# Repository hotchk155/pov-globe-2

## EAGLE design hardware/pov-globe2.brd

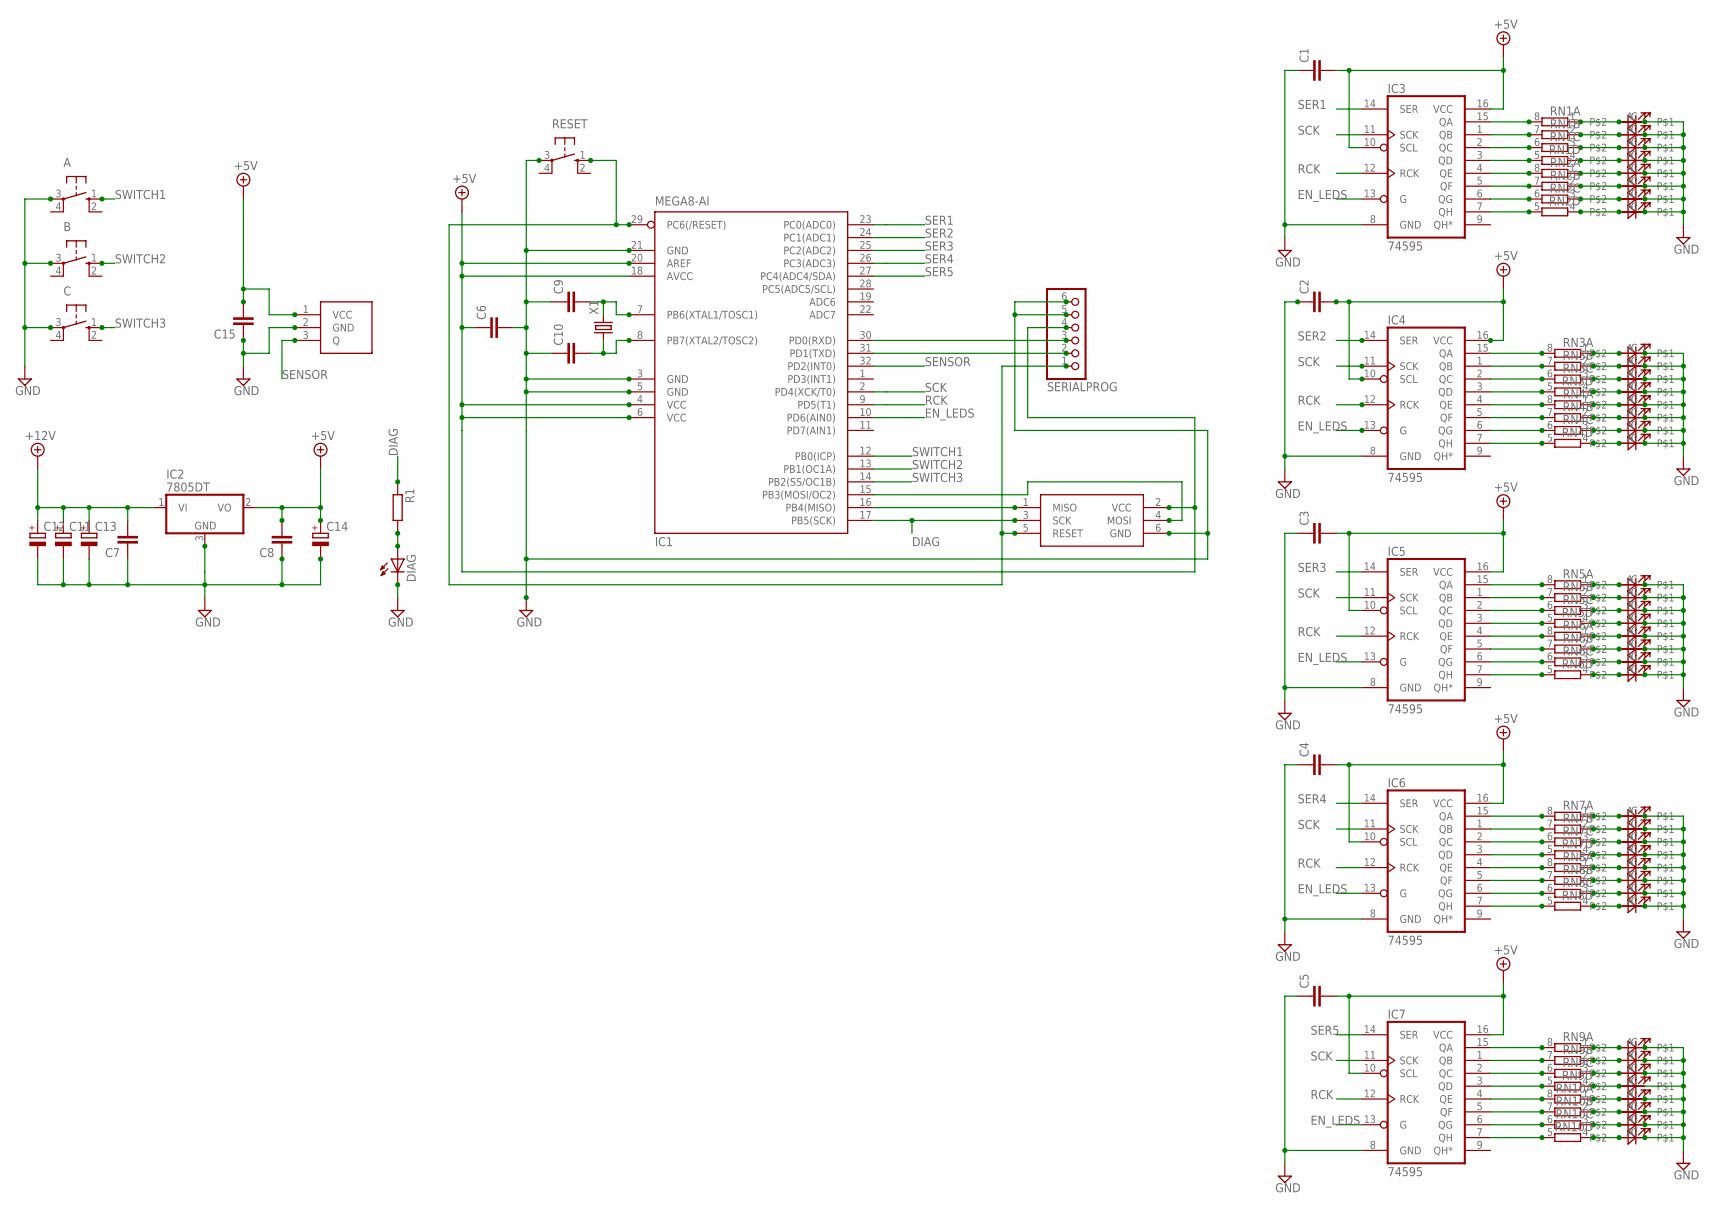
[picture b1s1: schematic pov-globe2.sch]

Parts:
0, 1, 2, 3, 4, 5, 6, 7, 8, 9, 10, 11, 12, 13, 14, 15, 16, 17, 18, 19, 20, 21, 22, 23, 24, 25, 26, 27, 28, 29, 30, 31, 32, 33, 34, 35, 36, 37, 38, 39: 3MMLEDSIDELED1_8MMSIDE; LED1_8MMSIDE
A: 10-XX; B3F-10XX
B: 10-XX; B3F-10XX
C: 10-XX; B3F-10XX
C1, C2, C3, C4, C5, C6, C7, C8, C9, C10, C15: C-EUC0805; C0805
C11, C12, C13, C14: CPOL-EUE2-5; E2-5
DIAG: LEDCHIP-LED0805; CHIP-LED0805
IC1: MEGA8-AI; TQFP32-08
IC2: 7805DT; TO252
IC3, IC4, IC5, IC6, IC7: 74595; TSSOP16
ICSP: TAG_CONN_AVR; TC2030-MCP-NL
R1: R-EU_R0805; R0805
RESET: 10-XX; B3F-10XX
RN1, RN2, RN3, RN4, RN5, RN6, RN7, RN8, RN9, RN10: 4R-N0603-ARC; 0603-ARC
S1: 3144HALLSWITCH
SERIALPROG: PINHD-1X6; 1X06
X1: CRYSTALHC49U-V; HC49U-V

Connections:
+5V: C1.2, C2.2, C3.2, C4.2, C5.2, C6.1, C8.2, C14.+, C15.2, IC1.4 (VCC), IC1.6 (VCC), IC1.18 (AVCC), IC1.20 (AREF), IC2.2 (VO), IC3.10 (SCL), IC3.16 (VCC), IC4.10 (SCL), IC4.16 (VCC), IC5.10 (SCL), IC5.16 (VCC), IC6.10 (SCL), IC6.16 (VCC), IC7.10 (SCL), IC7.16 (VCC), ICSP.2 (VCC), S1.1 (VCC), SERIALPROG.4
+12V: C7.2, C11.+, C12.+, C13.+, IC2.1 (VI)
DIAG: IC1.17 (PB5(SCK)), ICSP.3 (SCK), R1.1
EN_LEDS: IC1.10 (PD6(AIN0)), IC3.13 (G), IC4.13 (G), IC5.13 (G), IC6.13 (G), IC7.13 (G)
GND: 0.C, 1.C, 2.C, 3.C, 4.C, 5.C, 6.C, 7.C, 8.C, 9.C, 10.C, 11.C, 12.C, 13.C, 14.C, 15.C, 16.C, 17.C, 18.C, 19.C, 20.C, 21.C, 22.C, 23.C, 24.C, 25.C, 26.C, 27.C, 28.C, 29.C, 30.C, 31.C, 32.C, 33.C, 34.C, 35.C, 36.C, 37.C, 38.C, 39.C, A.3, B.3, C.3, C1.1, C2.1, C3.1, C4.1, C5.1, C6.2, C7.1, C8.1, C9.1, C10.1, C11.-, C12.-, C13.-, C14.-, C15.1, DIAG.C, IC1.3 (GND), IC1.5 (GND), IC1.21 (GND), IC2.3 (GND), IC3.8 (GND), IC4.8 (GND), IC5.8 (GND), IC6.8 (GND), IC7.8 (GND), ICSP.6 (GND), RESET.3, S1.2 (GND), SERIALPROG.5, SERIALPROG.6
unnamed: IC3.15 (QA), RN1.8 (2)
unnamed: IC3.1 (QB), RN1.7 (2)
unnamed: IC3.2 (QC), RN1.6 (2)
unnamed: IC3.3 (QD), RN1.5 (2)
unnamed: IC3.4 (QE), RN2.8 (2)
unnamed: IC3.5 (QF), RN2.7 (2)
unnamed: IC3.6 (QG), RN2.6 (2)
unnamed: IC3.7 (QH), RN2.5 (2)
unnamed: 0.A, RN1.1
unnamed: 1.A, RN1.2 (1)
unnamed: 2.A, RN1.3 (1)
unnamed: 3.A, RN1.4 (1)
unnamed: 4.A, RN2.1
unnamed: 5.A, RN2.2 (1)
unnamed: 6.A, RN2.3 (1)
unnamed: 7.A, RN2.4 (1)
unnamed: IC1.31 (PD1(TXD)), SERIALPROG.2
unnamed: IC1.30 (PD0(RXD)), SERIALPROG.3
unnamed: IC1.16 (PB4(MISO)), ICSP.1 (MISO)
unnamed: IC6.15 (QA), RN7.8 (2)
unnamed: IC1.15 (PB3(MOSI/OC2)), ICSP.4 (MOSI)
unnamed: IC6.1 (QB), RN7.7 (2)
unnamed: IC4.15 (QA), RN3.8 (2)
unnamed: IC4.1 (QB), RN3.7 (2)
unnamed: IC4.2 (QC), RN3.6 (2)
unnamed: IC4.3 (QD), RN3.5 (2)
unnamed: IC4.4 (QE), RN4.8 (2)
unnamed: IC4.5 (QF), RN4.7 (2)
unnamed: IC4.6 (QG), RN4.6 (2)
unnamed: IC4.7 (QH), RN4.5 (2)
unnamed: 8.A, RN3.1
unnamed: 9.A, RN3.2 (1)
unnamed: 10.A, RN3.3 (1)
unnamed: 11.A, RN3.4 (1)
unnamed: 12.A, RN4.1
unnamed: 13.A, RN4.2 (1)
unnamed: 14.A, RN4.3 (1)
unnamed: IC1.29 (PC6(/RESET)), ICSP.5 (RESET), RESET.1 (S), SERIALPROG.1
unnamed: DIAG.A, R1.2
unnamed: 15.A, RN4.4 (1)
unnamed: IC5.15 (QA), RN5.8 (2)
unnamed: IC5.1 (QB), RN5.7 (2)
unnamed: IC5.2 (QC), RN5.6 (2)
unnamed: IC5.3 (QD), RN5.5 (2)
unnamed: IC5.4 (QE), RN6.8 (2)
unnamed: IC5.5 (QF), RN6.7 (2)
unnamed: IC5.6 (QG), RN6.6 (2)
unnamed: IC5.7 (QH), RN6.5 (2)
unnamed: 16.A, RN5.1
unnamed: 17.A, RN5.2 (1)
unnamed: 18.A, RN5.3 (1)
unnamed: 19.A, RN5.4 (1)
unnamed: 20.A, RN6.1
unnamed: 21.A, RN6.2 (1)
unnamed: 22.A, RN6.3 (1)
unnamed: 23.A, RN6.4 (1)
unnamed: IC6.2 (QC), RN7.6 (2)
unnamed: IC6.3 (QD), RN7.5 (2)
unnamed: C9.2, IC1.7 (PB6(XTAL1/TOSC1)), X1.2
unnamed: C10.2, IC1.8 (PB7(XTAL2/TOSC2)), X1.1
unnamed: IC6.4 (QE), RN8.8 (2)
unnamed: IC6.5 (QF), RN8.7 (2)
unnamed: IC6.6 (QG), RN8.6 (2)
unnamed: IC6.7 (QH), RN8.5 (2)
unnamed: IC7.15 (QA), RN9.8 (2)
unnamed: 24.A, RN7.1
unnamed: 25.A, RN7.2 (1)
unnamed: 26.A, RN7.3 (1)
unnamed: 27.A, RN7.4 (1)
unnamed: 28.A, RN8.1
unnamed: 29.A, RN8.2 (1)
unnamed: 30.A, RN8.3 (1)
unnamed: 31.A, RN8.4 (1)
unnamed: IC7.1 (QB), RN9.7 (2)
unnamed: IC7.2 (QC), RN9.6 (2)
unnamed: IC7.3 (QD), RN9.5 (2)
unnamed: IC7.4 (QE), RN10.8 (2)
unnamed: IC7.5 (QF), RN10.7 (2)
unnamed: IC7.6 (QG), RN10.6 (2)
unnamed: IC7.7 (QH), RN10.5 (2)
unnamed: 32.A, RN9.1
unnamed: 33.A, RN9.2 (1)
unnamed: 34.A, RN9.3 (1)
unnamed: 35.A, RN9.4 (1)
unnamed: 36.A, RN10.1
unnamed: 37.A, RN10.2 (1)
unnamed: 38.A, RN10.3 (1)
unnamed: 39.A, RN10.4 (1)
RCK: IC1.9 (PD5(T1)), IC3.12 (RCK), IC4.12 (RCK), IC5.12 (RCK), IC6.12 (RCK), IC7.12 (RCK)
SCK: IC1.2 (PD4(XCK/T0)), IC3.11 (SCK), IC4.11 (SCK), IC5.11 (SCK), IC6.11 (SCK), IC7.11 (SCK)
SENSOR: IC1.32 (PD2(INT0)), S1.3 (Q)
SER1: IC1.23 (PC0(ADC0)), IC3.14 (SER)
SER2: IC1.24 (PC1(ADC1)), IC4.14 (SER)
SER3: IC1.25 (PC2(ADC2)), IC5.14 (SER)
SER4: IC1.26 (PC3(ADC3)), IC6.14 (SER)
SER5: IC1.27 (PC4(ADC4/SDA)), IC7.14 (SER)
SWITCH1: A.1 (S), IC1.12 (PB0(ICP))
SWITCH2: B.1 (S), IC1.13 (PB1(OC1A))
SWITCH3: C.1 (S), IC1.14 (PB2(SS/OC1B))

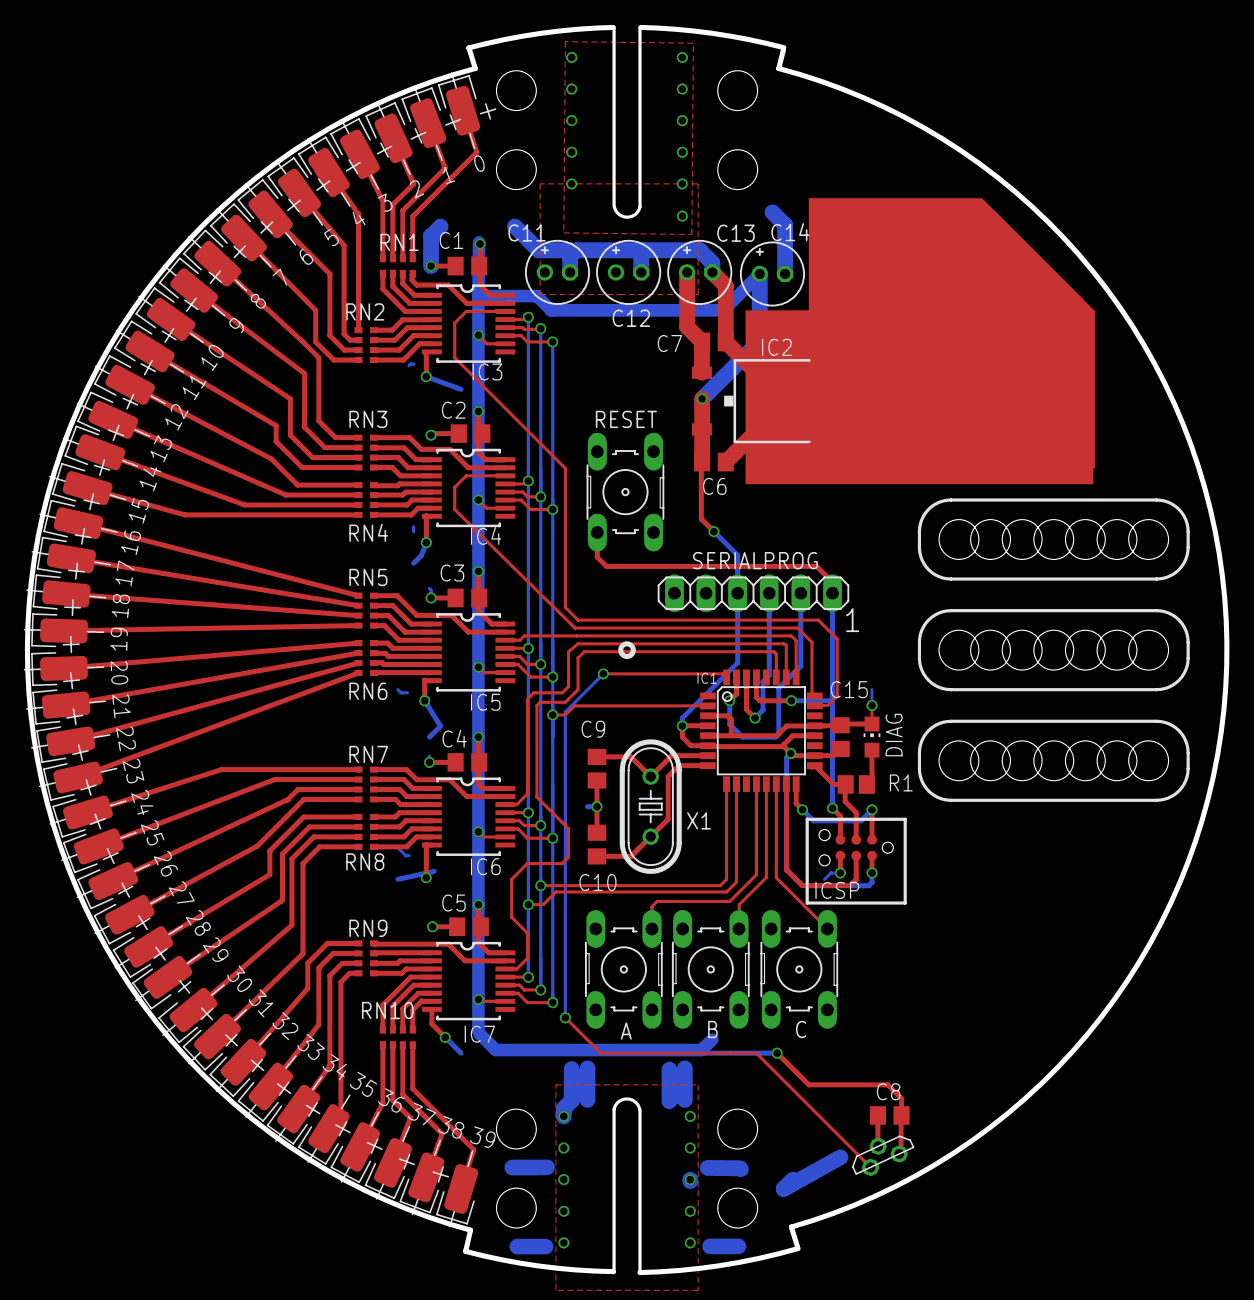
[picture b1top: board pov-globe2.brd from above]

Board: 2 copper layers, 96.4 x 100.1 mm, 82 parts (0 on the bottom side), 104 nets.

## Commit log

2015-05-29 :octocat: Added .gitattributes & .gitignore files
2015-05-29 initial commit at v2

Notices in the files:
parts and their libraries:
jasons_stuff: ©2009 ROFA.cz - modified and updated by Robert Darlington ‹rdarlington@gmail.com›
